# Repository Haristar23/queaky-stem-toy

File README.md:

# Queaky STEM Toy PCB

A custom PCB implementation of the **Queaky STEM Toy**, designed using **KiCad 10**. This project recreates the original NE555 Timer-based circuit on a compact printed circuit board, replacing the traditional perfboard implementation with a cleaner, more organized, and reliable PCB design.

---

## 📖 Overview

The Queaky STEM Toy is a simple electronic project that generates a squeaky sound using the **NE555 Timer IC**. This repository contains the complete schematic and PCB layout designed in KiCad 10.

This project was created to learn the complete PCB design workflow—from schematic capture to PCB layout and preparation for fabrication.

---

## ✨ Features

- Custom PCB designed in KiCad 10
- NE555 Timer-based circuit
- Compact PCB layout
- Through-hole components
- Simple and beginner-friendly design
- Ready for PCB fabrication

---

## 🔧 Components

| Component | Value |
|-----------|-------|
| Timer IC | NE555 |
| Resistor R1 | 1 kΩ |
| Resistor R2 | 10 kΩ |
| Capacitor C1 | 1 nF |
| Capacitor C2 | 100 µF |
| Battery Connector | 2-Pin |
| Touch Input | Header Pin |
| Buzzer Output | Header Pin |

---

## 📂 Repository Structure

```
Queaky-STEM-Toy-PCB/
├── queaky stem toy.kicad_sch
├── queaky stem toy.kicad_pcb
├── README.md
```

---

## 🛠 Software Used

- KiCad 10
- Git
- GitHub

---

## 📚 What I Learned

- Electronic circuit design
- Schematic capture in KiCad
- PCB footprint assignment
- Component placement
- PCB routing
- Design Rule Check (DRC)
- PCB 3D Viewer
- Preparing PCB files for fabrication

---

## 🚀 Future Improvements

- Optimize component placement
- Reduce PCB size
- Improve PCB routing
- Generate Gerber files
- Manufacture and test the PCB

---

## 👨‍💻 Author

**Harisudhan S**

Electronics and Communication Engineering Student

**Interests**
- Hardware Design
- PCB Design
- Embedded Systems
- Digital Electronics

---

## 📄 License

This project is shared for educational purposes.

---

⭐ If you found this project useful, consider giving it a star.

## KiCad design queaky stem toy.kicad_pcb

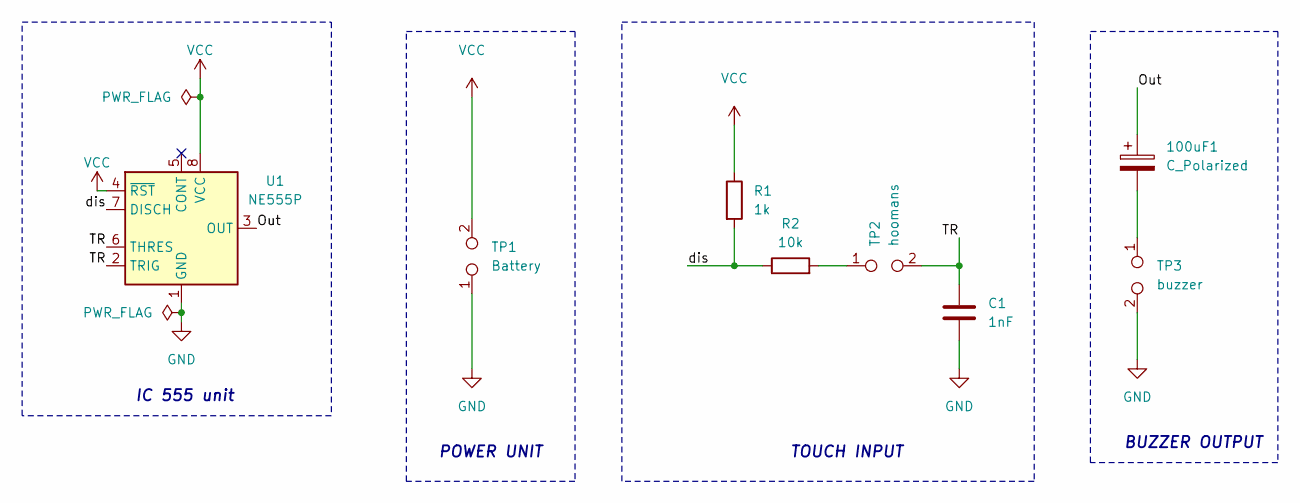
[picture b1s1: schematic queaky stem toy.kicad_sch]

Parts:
100uF1: C_Polarized; C_Disc_D9.0mm_W5.0mm_P10.00mm
C1: 1nF; CP_Radial_D8.0mm_P3.50mm
R1: 1k; R_Axial_DIN0207_L6.3mm_D2.5mm_P15.24mm_Horizontal
R2: 10k; R_Axial_DIN0207_L6.3mm_D2.5mm_P15.24mm_Horizontal
TP1: Battery; PinSocket_1x02_P2.54mm_Vertical
TP2: hoomans; PinSocket_1x02_P2.54mm_Vertical
TP3: buzzer; PinSocket_1x02_P2.54mm_Vertical
U1: NE555P; DIP-8_W7.62mm

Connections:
/Out: 100uF1.1, U1.3 (OUT)
/TR: C1.1, TP2.2, U1.2 (TRIG), U1.6 (THRES)
/dis: R1.2, R2.1, U1.7 (DISCH)
GND: C1.2, TP1.1, TP3.2, U1.1 (GND)
unnamed: 100uF1.2, TP3.1
unnamed: R2.2, TP2.1
VCC: R1.1, TP1.2, U1.4 (~RST), U1.8 (VCC)

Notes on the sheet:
POWER UNIT
BUZZER OUTPUT
TOUCH INPUT
IC 555 unit

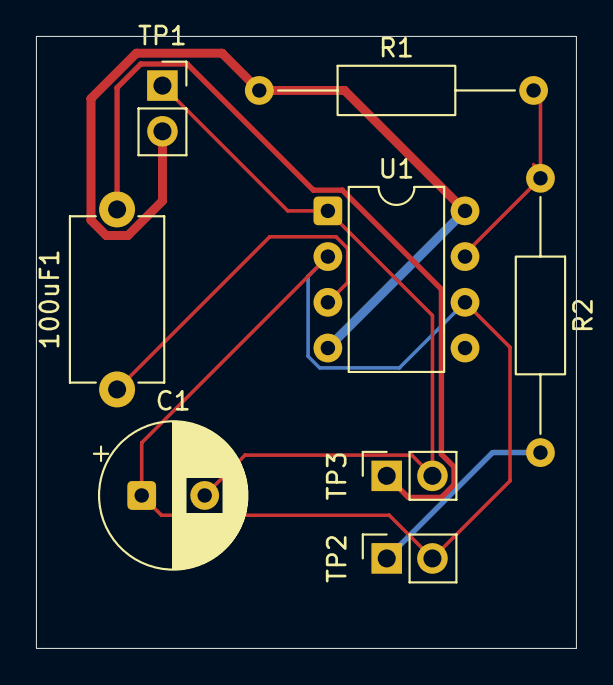
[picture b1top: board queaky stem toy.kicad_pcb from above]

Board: 2 copper layers, 30.0 x 34.0 mm, 8 parts (0 on the bottom side), 7 nets.
